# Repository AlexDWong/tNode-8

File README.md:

# tNode-8

The tNode-8 is an 8-universe ArtNet to DMX output node powered by a Texas Instruments Tiva-C microprocessor (TM4C1294NCPDT) and is currently in development. 

##Features

The tNode-8 is expected to include the following features:
* 8 DMX512 outputs
  * All outputs fused and optically and electrically isolated
  * Full RS485/DMX512 compliance
  * Screw terminals enabling end-user selection of 3-pin or 5-pin connectors
  * Individual universe assignment on each output
* 10/100Mbps Ethernet connectivity
* LCD character display and user input for settings adjustment
* 19"/1U rackmount enclousre
* PowerCON In/Thru
  * Auto-ranging power supply (100-240V, 50/60Hz)   
  * Input fuse

Potential features for future revisions may include (but are not limited to):
* DMX input capability
* Remote Device Management (RDM)
* Remote node configuration (LAN-based)
* Physical lockout switch
* Expansion to 16 universes of DMX I/O

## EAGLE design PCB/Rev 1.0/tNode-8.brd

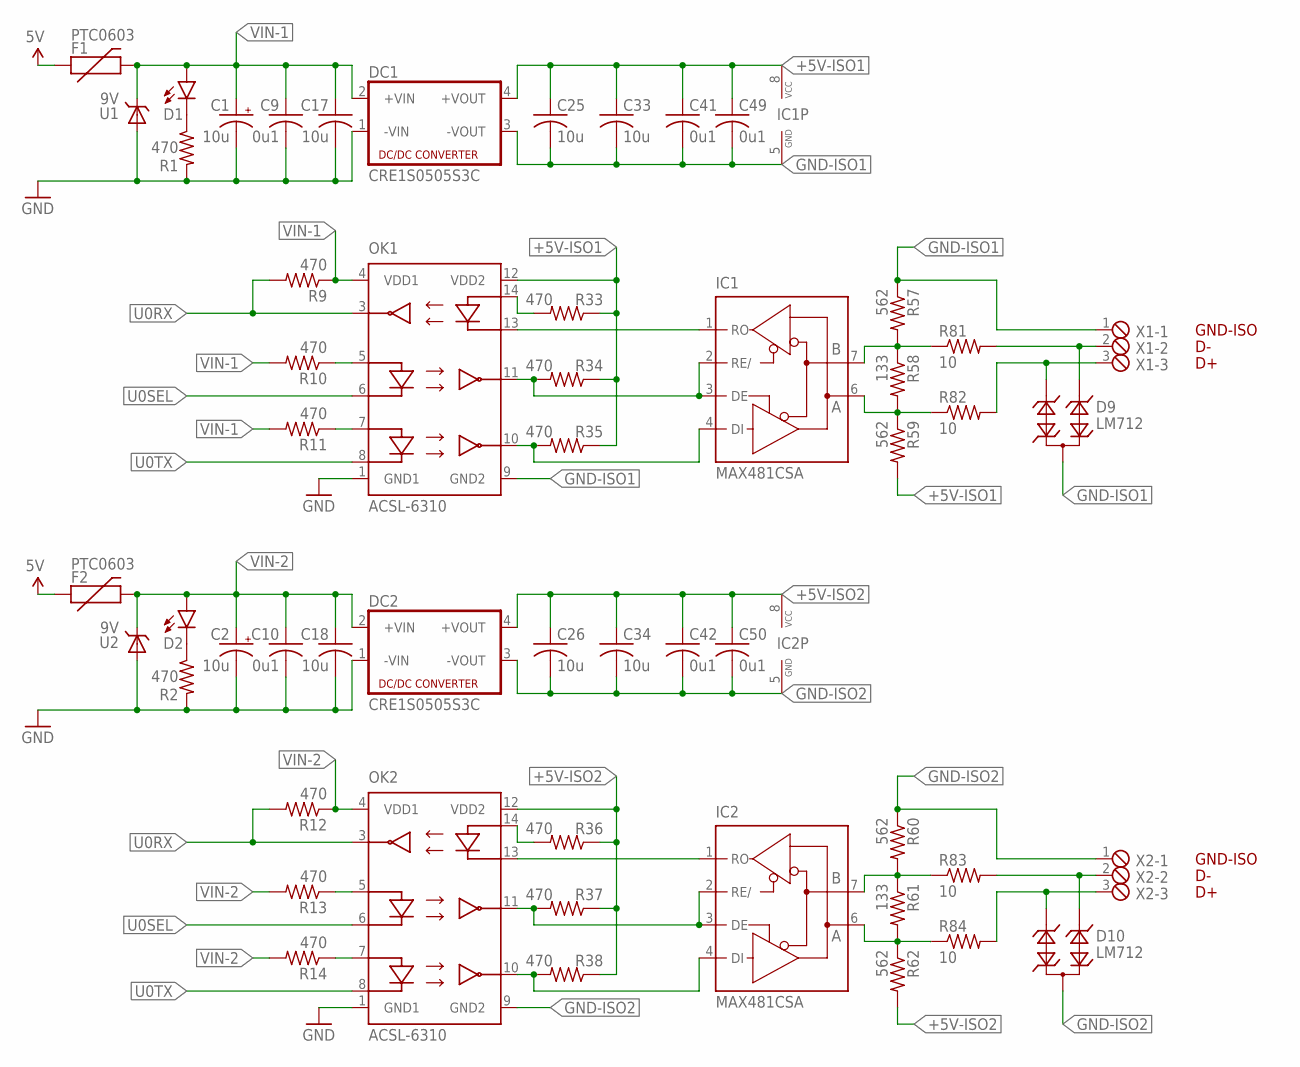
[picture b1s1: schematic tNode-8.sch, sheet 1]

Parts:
C1, C2: 10u; E2,5-5-NOSILK
C9, C10, C41, C42, C49, C50: 0u1; C0603K
C17, C18, C25, C26, C33, C34: 10u; C0603K
D1, D2: LED0603; LED-0603
D9, D10: LM712; SOT23
DC1, DC2: CRE1S0505S3C; 4SIL
F1, F2: PTC0603; 0603
IC1, IC2: MAX481CSA; SO08
OK1, OK2: ACSL-6310; SO-16
R1, R2, R9, R10, R11, R12, R13, R14, R33, R34, R35, R36, R37, R38: 470; R0603
R57, R59, R60, R62: 562; R0603
R58, R61: 133; R0603
R81, R82, R83, R84: 10; R0603
U1, U2: 9V; SOD323-NOSILK
X1, X2: MPT3; 3POL254

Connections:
5V: F1.1, F2.1; also elsewhere on the board
+5V-ISO1: C25.1, C33.1, C41.1, C49.1, DC1.4 (+VOUT), IC1.8 (VCC), OK1.12 (VDD2), R33.1, R34.1, R35.1, R59.2
+5V-ISO2: C26.1, C34.1, C42.1, C50.1, DC2.4 (+VOUT), IC2.8 (VCC), OK2.12 (VDD2), R36.1, R37.1, R38.1, R62.2
GND: C1.-, C2.-, C9.2, C10.2, C17.2, C18.2, DC1.1 (-VIN), DC2.1 (-VIN), OK1.1 (GND1), OK2.1 (GND1), R1.2, R2.2, U1.A, U2.A; also elsewhere on the board
GND-ISO1: C25.2, C33.2, C41.2, C49.2, D9.3, DC1.3 (-VOUT), IC1.5 (GND), OK1.9 (GND2), R57.1, X1.1
GND-ISO2: C26.2, C34.2, C42.2, C50.2, D10.3, DC2.3 (-VOUT), IC2.5 (GND), OK2.9 (GND2), R60.1, X2.1
unnamed: IC2.7 (B), R60.2, R61.1, R83.1
unnamed: IC1.7 (B), R57.2, R58.1, R81.1
unnamed: IC1.6 (A), R58.2, R59.1, R82.1
unnamed: IC2.6 (A), R61.2, R62.1, R84.1
unnamed: IC2.1 (RO), OK2.13 (C3)
unnamed: IC2.2 (RE/), IC2.3 (DE), OK2.11 (VO1), R37.2
unnamed: OK2.5 (A1), R13.1
unnamed: OK2.7 (A2), R14.1
unnamed: OK2.14 (A3), R36.2
unnamed: IC1.1 (RO), OK1.13 (C3)
unnamed: D2.C, R2.1
unnamed: D10.1, R83.2, X2.2
unnamed: D10.2, R84.2, X2.3
unnamed: IC1.2 (RE/), IC1.3 (DE), OK1.11 (VO1), R34.2
unnamed: OK1.5 (A1), R10.1
unnamed: OK1.7 (A2), R11.1
unnamed: OK1.14 (A3), R33.2
unnamed: D1.C, R1.1
unnamed: D9.1, R81.2, X1.2
unnamed: D9.2, R82.2, X1.3
OPTO-OUT1: IC1.4 (DI), OK1.10 (VO2), R35.2
OPTO-OUT2: IC2.4 (DI), OK2.10 (VO2), R38.2
U0RX: OK1.3 (V03), OK2.3 (V03), R9.2, R12.2; also elsewhere on the board
U0SEL: OK1.6 (C1), OK2.6 (C1); also elsewhere on the board
U0TX: OK1.8 (C2), OK2.8 (C2); also elsewhere on the board
VIN-1: C1.+, C9.1, C17.1, D1.A, DC1.2 (+VIN), F1.2, OK1.4 (VDD1), R9.1, R10.2, R11.2, U1.C
VIN-2: C2.+, C10.1, C18.1, D2.A, DC2.2 (+VIN), F2.2, OK2.4 (VDD1), R12.1, R13.2, R14.2, U2.C

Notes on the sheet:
GND-ISO

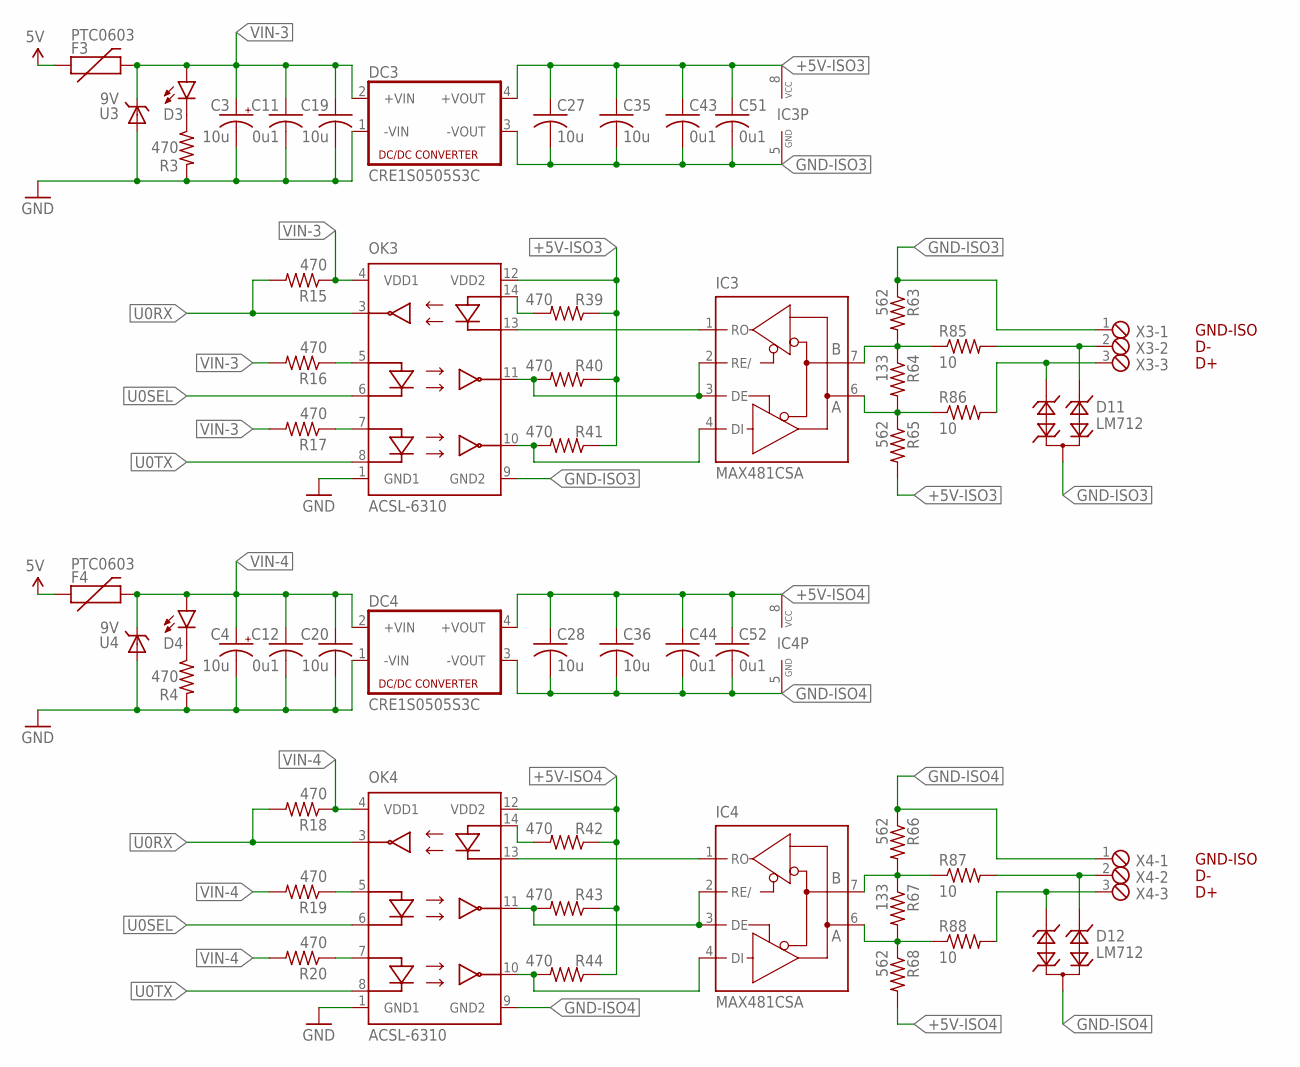
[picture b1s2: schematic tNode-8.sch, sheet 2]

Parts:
C3, C4: 10u; E2,5-5-NOSILK
C11, C12, C43, C44, C51, C52: 0u1; C0603K
C19, C20, C27, C28, C35, C36: 10u; C0603K
D3, D4: LED0603; LED-0603
D11, D12: LM712; SOT23
DC3, DC4: CRE1S0505S3C; 4SIL
F3, F4: PTC0603; 0603
IC3, IC4: MAX481CSA; SO08
OK3, OK4: ACSL-6310; SO-16
R3, R4, R15, R16, R17, R18, R19, R20, R39, R40, R41, R42, R43, R44: 470; R0603
R63, R65, R66, R68: 562; R0603
R64, R67: 133; R0603
R85, R86, R87, R88: 10; R0603
U3, U4: 9V; SOD323-NOSILK
X3, X4: MPT3; 3POL254

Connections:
5V: F3.1, F4.1; also elsewhere on the board
+5V-ISO3: C27.1, C35.1, C43.1, C51.1, DC3.4 (+VOUT), IC3.8 (VCC), OK3.12 (VDD2), R39.1, R40.1, R41.1, R65.2
+5V-ISO4: C28.1, C36.1, C44.1, C52.1, DC4.4 (+VOUT), IC4.8 (VCC), OK4.12 (VDD2), R42.1, R43.1, R44.1, R68.2
GND: C3.-, C4.-, C11.2, C12.2, C19.2, C20.2, DC3.1 (-VIN), DC4.1 (-VIN), OK3.1 (GND1), OK4.1 (GND1), R3.2, R4.2, U3.A, U4.A; also elsewhere on the board
GND-ISO3: C27.2, C35.2, C43.2, C51.2, D11.3, DC3.3 (-VOUT), IC3.5 (GND), OK3.9 (GND2), R63.1, X3.1
GND-ISO4: C28.2, C36.2, C44.2, C52.2, D12.3, DC4.3 (-VOUT), IC4.5 (GND), OK4.9 (GND2), R66.1, X4.1
unnamed: IC3.7 (B), R63.2, R64.1, R85.1
unnamed: IC3.6 (A), R64.2, R65.1, R86.1
unnamed: IC3.1 (RO), OK3.13 (C3)
unnamed: IC3.2 (RE/), IC3.3 (DE), OK3.11 (VO1), R40.2
unnamed: OK3.5 (A1), R16.1
unnamed: OK3.7 (A2), R17.1
unnamed: OK3.14 (A3), R39.2
unnamed: D3.C, R3.1
unnamed: D11.1, R85.2, X3.2
unnamed: D11.2, R86.2, X3.3
unnamed: IC4.7 (B), R66.2, R67.1, R87.1
unnamed: IC4.6 (A), R67.2, R68.1, R88.1
unnamed: IC4.1 (RO), OK4.13 (C3)
unnamed: IC4.2 (RE/), IC4.3 (DE), OK4.11 (VO1), R43.2
unnamed: OK4.5 (A1), R19.1
unnamed: OK4.7 (A2), R20.1
unnamed: OK4.14 (A3), R42.2
unnamed: D4.C, R4.1
unnamed: D12.1, R87.2, X4.2
unnamed: D12.2, R88.2, X4.3
OPTO-OUT3: IC3.4 (DI), OK3.10 (VO2), R41.2
OPTO-OUT4: IC4.4 (DI), OK4.10 (VO2), R44.2
U0RX: OK3.3 (V03), OK4.3 (V03), R15.2, R18.2; also elsewhere on the board
U0SEL: OK3.6 (C1), OK4.6 (C1); also elsewhere on the board
U0TX: OK3.8 (C2), OK4.8 (C2); also elsewhere on the board
VIN-3: C3.+, C11.1, C19.1, D3.A, DC3.2 (+VIN), F3.2, OK3.4 (VDD1), R15.1, R16.2, R17.2, U3.C
VIN-4: C4.+, C12.1, C20.1, D4.A, DC4.2 (+VIN), F4.2, OK4.4 (VDD1), R18.1, R19.2, R20.2, U4.C

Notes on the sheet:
GND-ISO

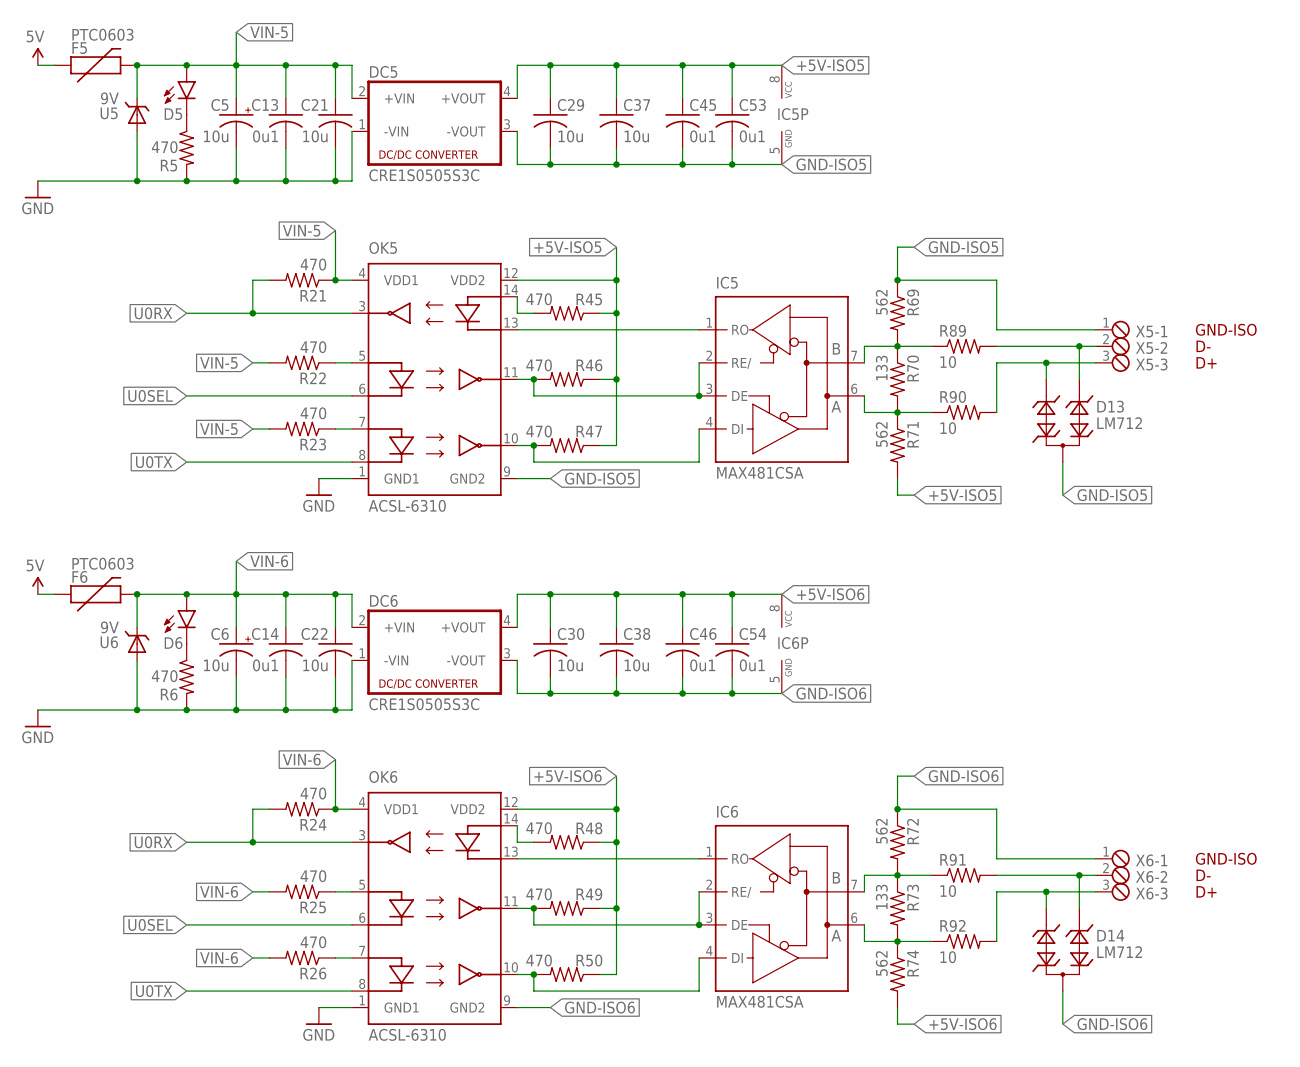
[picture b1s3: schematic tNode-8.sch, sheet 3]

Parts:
C5, C6: 10u; E2,5-5-NOSILK
C13, C14, C45, C46, C53, C54: 0u1; C0603K
C21, C22, C29, C30, C37, C38: 10u; C0603K
D5, D6: LED0603; LED-0603
D13, D14: LM712; SOT23
DC5, DC6: CRE1S0505S3C; 4SIL
F5, F6: PTC0603; 0603
IC5, IC6: MAX481CSA; SO08
OK5, OK6: ACSL-6310; SO-16
R5, R6, R21, R22, R23, R24, R25, R26, R45, R46, R47, R48, R49, R50: 470; R0603
R69, R71, R72, R74: 562; R0603
R70, R73: 133; R0603
R89, R90, R91, R92: 10; R0603
U5, U6: 9V; SOD323-NOSILK
X5, X6: MPT3; 3POL254

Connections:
5V: F5.1, F6.1; also elsewhere on the board
+5V-ISO5: C29.1, C37.1, C45.1, C53.1, DC5.4 (+VOUT), IC5.8 (VCC), OK5.12 (VDD2), R45.1, R46.1, R47.1, R71.2
+5V-ISO6: C30.1, C38.1, C46.1, C54.1, DC6.4 (+VOUT), IC6.8 (VCC), OK6.12 (VDD2), R48.1, R49.1, R50.1, R74.2
GND: C5.-, C6.-, C13.2, C14.2, C21.2, C22.2, DC5.1 (-VIN), DC6.1 (-VIN), OK5.1 (GND1), OK6.1 (GND1), R5.2, R6.2, U5.A, U6.A; also elsewhere on the board
GND-ISO5: C29.2, C37.2, C45.2, C53.2, D13.3, DC5.3 (-VOUT), IC5.5 (GND), OK5.9 (GND2), R69.1, X5.1
GND-ISO6: C30.2, C38.2, C46.2, C54.2, D14.3, DC6.3 (-VOUT), IC6.5 (GND), OK6.9 (GND2), R72.1, X6.1
unnamed: IC5.7 (B), R69.2, R70.1, R89.1
unnamed: IC5.6 (A), R70.2, R71.1, R90.1
unnamed: IC5.1 (RO), OK5.13 (C3)
unnamed: IC5.2 (RE/), IC5.3 (DE), OK5.11 (VO1), R46.2
unnamed: OK5.5 (A1), R22.1
unnamed: OK5.7 (A2), R23.1
unnamed: OK5.14 (A3), R45.2
unnamed: D5.C, R5.1
unnamed: D13.1, R89.2, X5.2
unnamed: D13.2, R90.2, X5.3
unnamed: IC6.7 (B), R72.2, R73.1, R91.1
unnamed: IC6.6 (A), R73.2, R74.1, R92.1
unnamed: IC6.1 (RO), OK6.13 (C3)
unnamed: IC6.2 (RE/), IC6.3 (DE), OK6.11 (VO1), R49.2
unnamed: OK6.5 (A1), R25.1
unnamed: OK6.7 (A2), R26.1
unnamed: OK6.14 (A3), R48.2
unnamed: D6.C, R6.1
unnamed: D14.1, R91.2, X6.2
unnamed: D14.2, R92.2, X6.3
OPTO-OUT5: IC5.4 (DI), OK5.10 (VO2), R47.2
OPTO-OUT6: IC6.4 (DI), OK6.10 (VO2), R50.2
U0RX: OK5.3 (V03), OK6.3 (V03), R21.2, R24.2; also elsewhere on the board
U0SEL: OK5.6 (C1), OK6.6 (C1); also elsewhere on the board
U0TX: OK5.8 (C2), OK6.8 (C2); also elsewhere on the board
VIN-5: C5.+, C13.1, C21.1, D5.A, DC5.2 (+VIN), F5.2, OK5.4 (VDD1), R21.1, R22.2, R23.2, U5.C
VIN-6: C6.+, C14.1, C22.1, D6.A, DC6.2 (+VIN), F6.2, OK6.4 (VDD1), R24.1, R25.2, R26.2, U6.C

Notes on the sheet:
GND-ISO

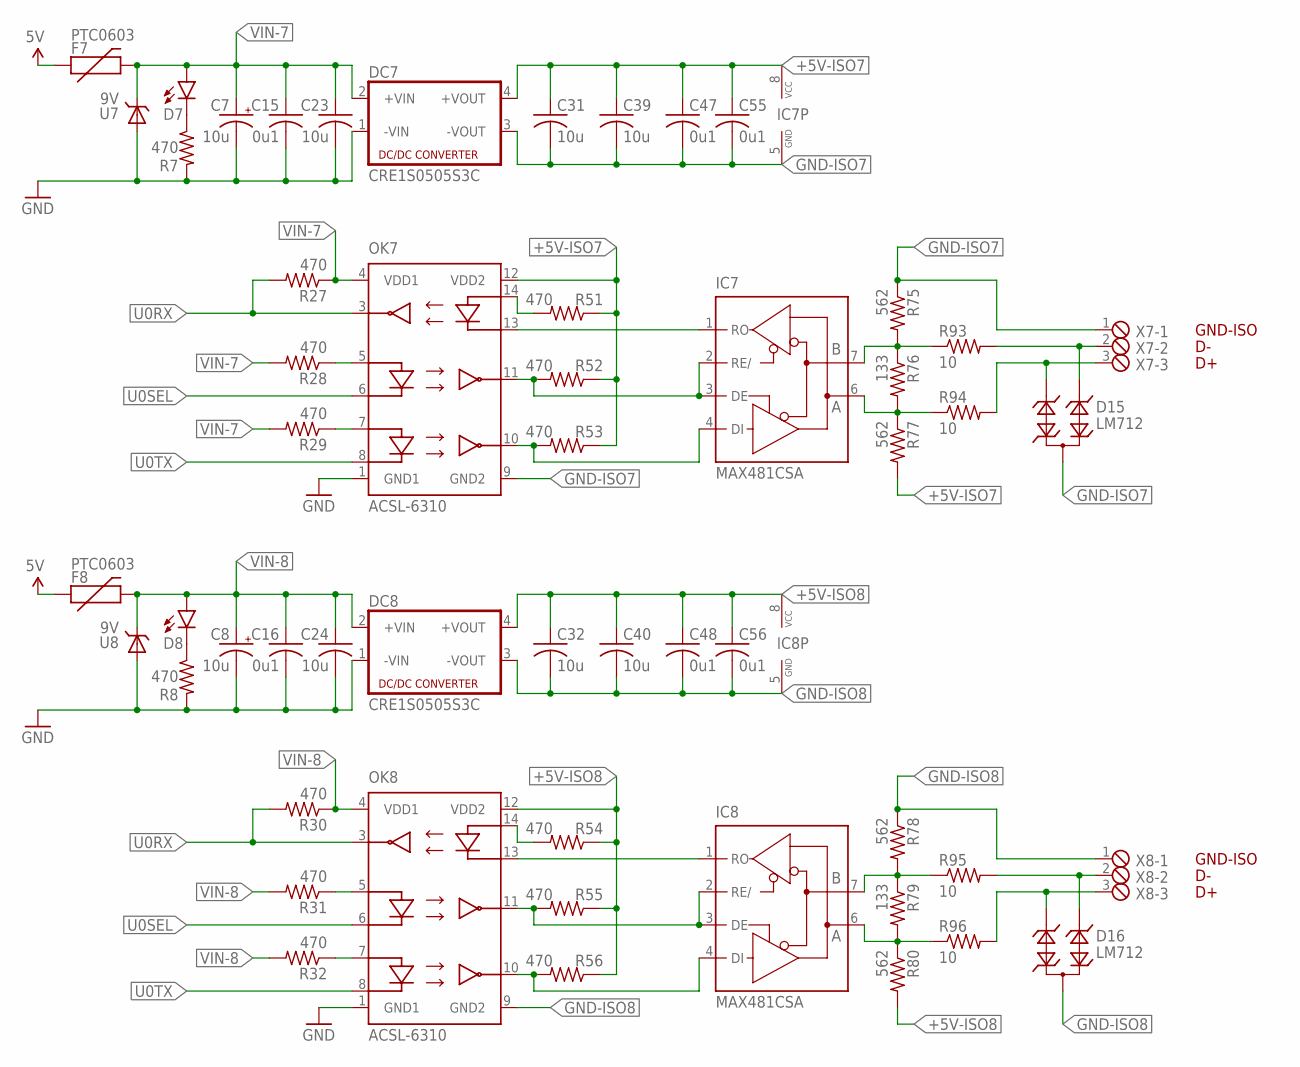
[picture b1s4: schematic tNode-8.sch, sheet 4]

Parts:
C7, C8: 10u; E2,5-5-NOSILK
C15, C16, C47, C48, C55, C56: 0u1; C0603K
C23, C24, C31, C32, C39, C40: 10u; C0603K
D7, D8: LED0603; LED-0603
D15, D16: LM712; SOT23
DC7, DC8: CRE1S0505S3C; 4SIL
F7, F8: PTC0603; 0603
IC7, IC8: MAX481CSA; SO08
OK7, OK8: ACSL-6310; SO-16
R7, R8, R27, R28, R29, R30, R31, R32, R51, R52, R53, R54, R55, R56: 470; R0603
R75, R77, R78, R80: 562; R0603
R76, R79: 133; R0603
R93, R94, R95, R96: 10; R0603
U7, U8: 9V; SOD323-NOSILK
X7, X8: MPT3; 3POL254

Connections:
5V: F7.1, F8.1; also elsewhere on the board
+5V-ISO7: C31.1, C39.1, C47.1, C55.1, DC7.4 (+VOUT), IC7.8 (VCC), OK7.12 (VDD2), R51.1, R52.1, R53.1, R77.2
+5V-ISO8: C32.1, C40.1, C48.1, C56.1, DC8.4 (+VOUT), IC8.8 (VCC), OK8.12 (VDD2), R54.1, R55.1, R56.1, R80.2
GND: C7.-, C8.-, C15.2, C16.2, C23.2, C24.2, DC7.1 (-VIN), DC8.1 (-VIN), OK7.1 (GND1), OK8.1 (GND1), R7.2, R8.2, U7.A, U8.A; also elsewhere on the board
GND-ISO7: C31.2, C39.2, C47.2, C55.2, D15.3, DC7.3 (-VOUT), IC7.5 (GND), OK7.9 (GND2), R75.1, X7.1
GND-ISO8: C32.2, C40.2, C48.2, C56.2, D16.3, DC8.3 (-VOUT), IC8.5 (GND), OK8.9 (GND2), R78.1, X8.1
unnamed: IC7.7 (B), R75.2, R76.1, R93.1
unnamed: IC7.6 (A), R76.2, R77.1, R94.1
unnamed: IC7.1 (RO), OK7.13 (C3)
unnamed: IC7.2 (RE/), IC7.3 (DE), OK7.11 (VO1), R52.2
unnamed: OK7.5 (A1), R28.1
unnamed: OK7.7 (A2), R29.1
unnamed: OK7.14 (A3), R51.2
unnamed: D7.C, R7.1
unnamed: D15.1, R93.2, X7.2
unnamed: D15.2, R94.2, X7.3
unnamed: IC8.7 (B), R78.2, R79.1, R95.1
unnamed: IC8.6 (A), R79.2, R80.1, R96.1
unnamed: IC8.1 (RO), OK8.13 (C3)
unnamed: IC8.2 (RE/), IC8.3 (DE), OK8.11 (VO1), R55.2
unnamed: OK8.5 (A1), R31.1
unnamed: OK8.7 (A2), R32.1
unnamed: OK8.14 (A3), R54.2
unnamed: D8.C, R8.1
unnamed: D16.1, R95.2, X8.2
unnamed: D16.2, R96.2, X8.3
OPTO-OUT7: IC7.4 (DI), OK7.10 (VO2), R53.2
OPTO-OUT8: IC8.4 (DI), OK8.10 (VO2), R56.2
U0RX: OK7.3 (V03), OK8.3 (V03), R27.2, R30.2; also elsewhere on the board
U0SEL: OK7.6 (C1), OK8.6 (C1); also elsewhere on the board
U0TX: OK7.8 (C2), OK8.8 (C2); also elsewhere on the board
VIN-7: C7.+, C15.1, C23.1, D7.A, DC7.2 (+VIN), F7.2, OK7.4 (VDD1), R27.1, R28.2, R29.2, U7.C
VIN-8: C8.+, C16.1, C24.1, D8.A, DC8.2 (+VIN), F8.2, OK8.4 (VDD1), R30.1, R31.2, R32.2, U8.C

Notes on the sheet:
GND-ISO

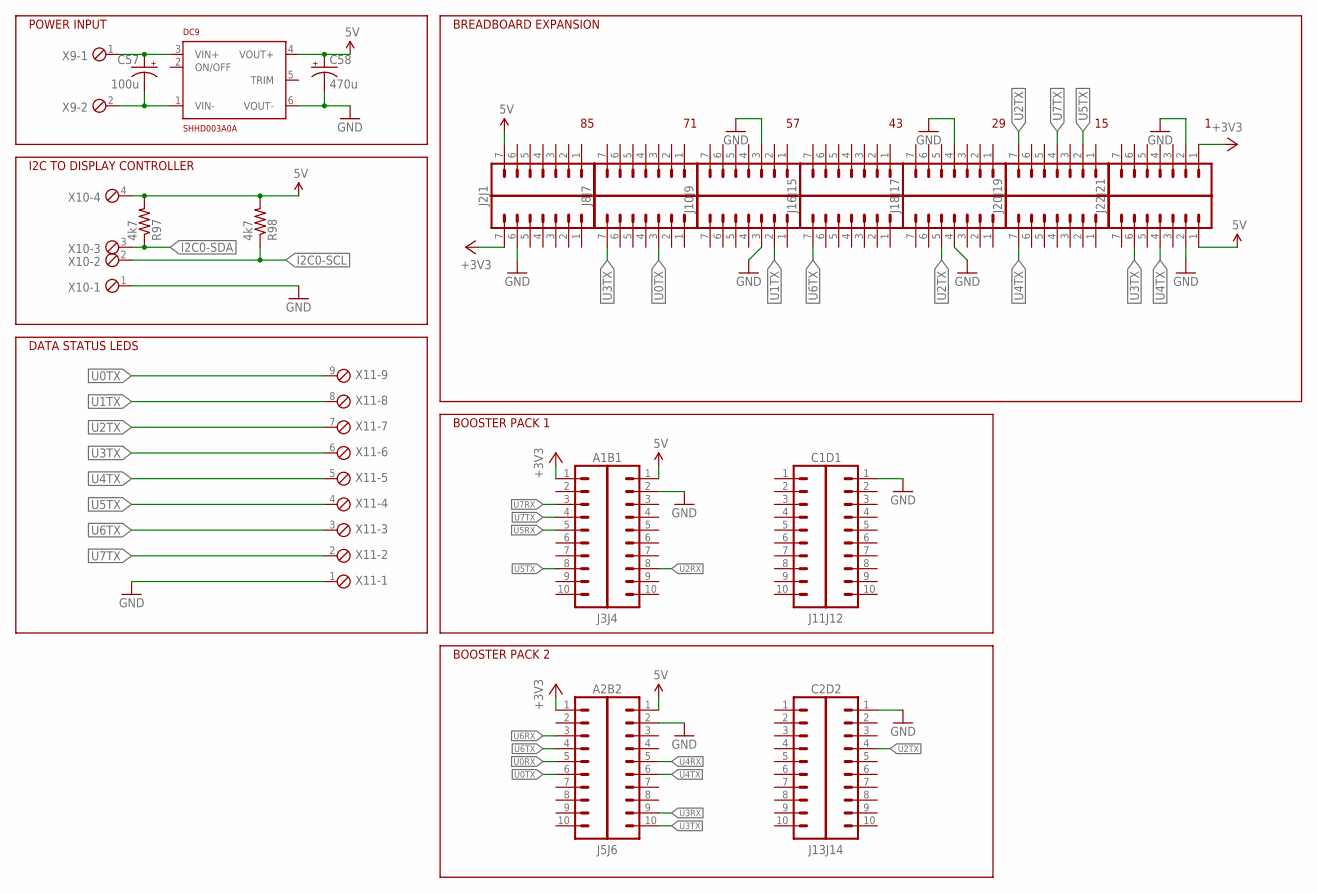
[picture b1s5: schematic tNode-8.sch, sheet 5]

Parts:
C57: 100u; PANASONIC_D
C58: 470u; PANASONIC_D
DC9: SHHD003A0A
J1, J2, J7, J8, J9, J10, J15, J16, J17, J18, J19, J20, J21, J22: M07; 1X07
J3: A1; 1X10
J4: B1; 1X10
J5: A2; 1X10
J6: B2; 1X10
J11: C1; 1X10
J12: D1; 1X10
J13: C2; 1X10
J14: D2; 1X10
R97, R98: 4k7; R0603
X9: MPT2; 2POL254
X10: MPT4; 4POL254
X11: MPT9; 9POL254

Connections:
5V: C58.+, DC9.4 (VOUT+), J1.7, J4.1, J6.1, J22.1, R97.2, R98.2, X10.4; also elsewhere on the board
+3V3: J2.7, J3.1, J5.1, J21.1
GND: C58.-, DC9.6 (VOUT-), J2.6, J4.2, J6.2, J9.3, J10.3, J12.1, J14.1, J17.4, J18.4, J21.2, J22.2, X10.1, X11.1; also elsewhere on the board
I2C0-SCL: R98.1, X10.2
I2C0-SDA: R97.1, X10.3
unnamed: C57.-, DC9.1 (VIN-), X9.2
unnamed: C57.+, DC9.3 (VIN+), X9.1
U0RX: J5.5; also elsewhere on the board
U0TX: J5.6, J8.3, X11.9; also elsewhere on the board
U1TX: J10.2, X11.8
U2RX: J4.8
U2TX: J14.4, J18.5, J19.7, X11.7
U3RX: J6.9
U3TX: J6.10, J8.7, J22.6, X11.6
U4RX: J6.5
U4TX: J6.6, J20.7, J22.4, X11.5
U5RX: J3.5
U5TX: J3.8, J19.2, X11.4
U6RX: J5.3
U6TX: J5.4, J16.7, X11.3
U7RX: J3.3
U7TX: J3.4, J19.4, X11.2

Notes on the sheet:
POWER INPUT
BOOSTER PACK 1
BOOSTER PACK 2
BREADBOARD EXPANSION
I2C TO DISPLAY CONTROLLER
DATA STATUS LEDS

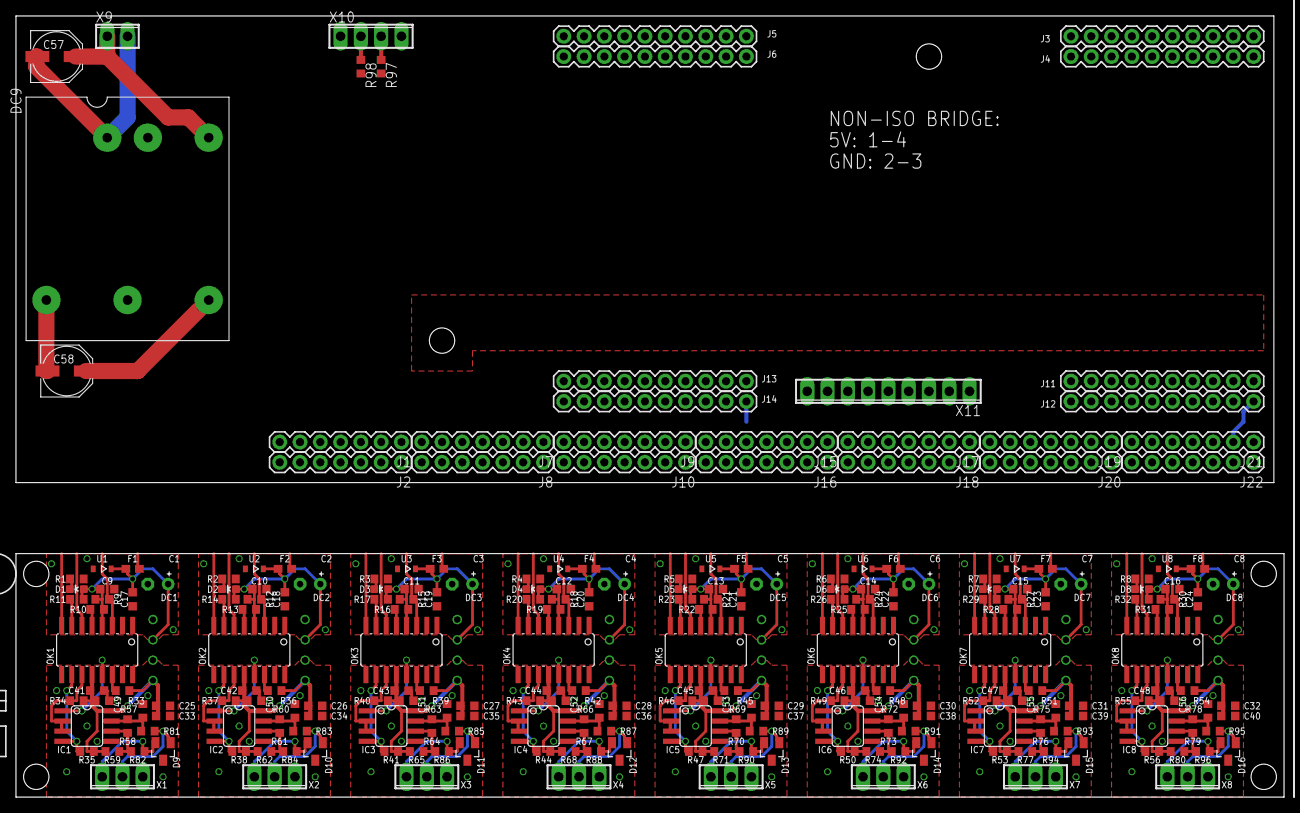
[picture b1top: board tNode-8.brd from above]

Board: 2 copper layers, 158.8 x 30.5 mm, 246 parts (0 on the bottom side), 129 nets.

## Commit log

2016-08-27 Initial description
2016-09-17 [WIP] PCB Rev 1.0
2016-09-17 ignore EAGLE .lck and Excel files
2016-09-17 Exclude EAGLE autosave and .SCR
2016-09-17 [WIP] add all UART-DMX outputs

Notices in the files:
parts and their libraries:
SparkFun-Connectors: Licensing: Creative Commons ShareAlike 4.0 International - https://creativecommons.org/licenses/by-sa/4.0
